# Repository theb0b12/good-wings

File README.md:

# Good Wings

- A unibody keyboard
1. basically a corne unibody with stagger

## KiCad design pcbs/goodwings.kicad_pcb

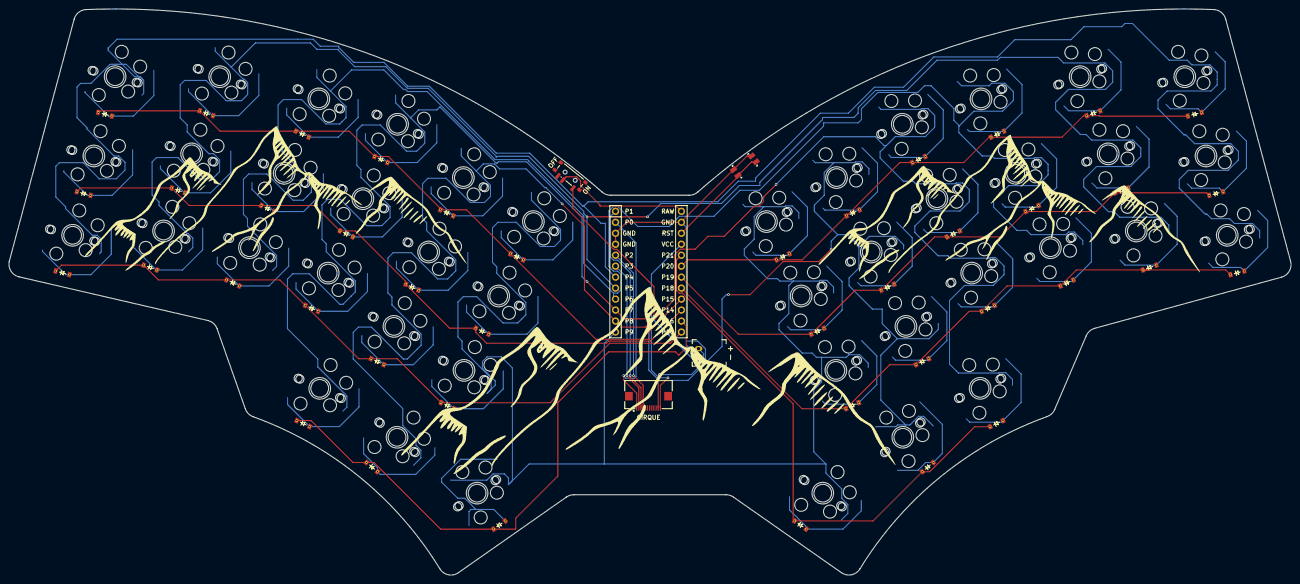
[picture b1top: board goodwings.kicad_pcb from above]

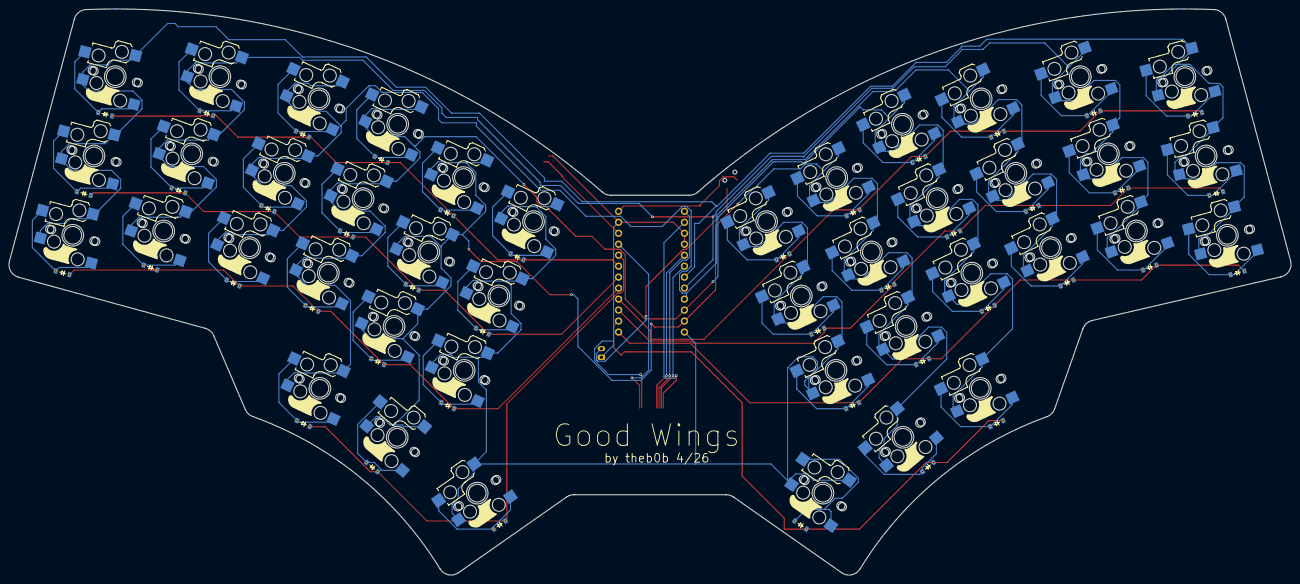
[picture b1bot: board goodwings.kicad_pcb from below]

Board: 2 copper layers, 296.7 x 131.0 mm, 131 parts (84 on the bottom side), 65 nets.

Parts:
D1, D2, D3, D4, D5, D6, D7, D8, D9, D10, D11, D12, D13, D14, D15, D16, D17, D18, D19, D20, D21, D22, D23, D24, D25, D26, D27, D28, D29, D30, D31, D32, D33, D34, D35, D36, D37, D38, D39, D40, D41, D42: ComboDiode
J2: CIRQUE; FPC-SMD_FPC05012-09200-.5mm-rev
JST1: battery_connector_jst_ph_2
MCU1: mcu_nice_nano
PWR1: power_switch_smd_side
RST1: reset_switch_smd_side
S1, S2, S3, S4, S5, S6, S7, S8, S9, S10, S11, S12, S13, S14, S15, S16, S17, S18, S19, S20, S21, S22, S23, S24, S25, S26, S27, S28, S29, S30, S31, S32, S33, S34, S35, S36, S37, S38, S39, S40, S41, S42: switch_choc_v1_v2
S43, S44, S45, S46, S47, S48, S49, S50, S51, S52, S53, S54, S55, S56, S57, S58, S59, S60, S61, S62, S63, S64, S65, S66, S67, S68, S69, S70, S71, S72, S73, S74, S75, S76, S77, S78, S79, S80, S81, S82, S83, S84: switch_mx

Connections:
BAT_P: JST1.2, PWR1.1
GND: J2.2, JST1.1, MCU1.2, MCU1.21, MCU1.22, RST1.1, RST1.3
P0: J2.12, MCU1.23
P1: J2.10, MCU1.24
P2: J2.9, MCU1.20
P3: J2.11, MCU1.19
P4: MCU1.18, S1.1, S2.1, S3.1, S22.1, S23.1, S24.1, S43.1, S44.1, S45.1, S64.1, S65.1, S66.1
P5: MCU1.17, S4.1, S5.1, S6.1, S25.1, S26.1, S27.1, S46.1, S47.1, S48.1, S67.1, S68.1, S69.1
P6: MCU1.16, S7.1, S8.1, S9.1, S28.1, S29.1, S30.1, S49.1, S50.1, S51.1, S70.1, S71.1, S72.1
P7: MCU1.15, S10.1, S11.1, S12.1, S19.1, S31.1, S32.1, S33.1, S40.1, S52.1, S53.1, S54.1, S61.1, S73.1, S74.1, S75.1, S82.1
P8: MCU1.14, S13.1, S14.1, S15.1, S20.1, S34.1, S35.1, S36.1, S41.1, S55.1, S56.1, S57.1, S62.1, S76.1, S77.1, S78.1, S83.1
P9: MCU1.13, S16.1, S17.1, S18.1, S21.1, S37.1, S38.1, S39.1, S42.1, S58.1, S59.1, S60.1, S63.1, S79.1, S80.1, S81.1, S84.1
P10: D1.1, D4.1, D7.1, D10.1, D13.1, D16.1, MCU1.12
P14: D2.1, D5.1, D8.1, D11.1, D14.1, D17.1, MCU1.10
P15: D3.1, D6.1, D9.1, D12.1, D15.1, D18.1, MCU1.9
P16: D19.1, D20.1, D21.1, MCU1.11
P18: D22.1, D25.1, D28.1, D31.1, D34.1, D37.1, MCU1.8
P19: D23.1, D26.1, D29.1, D32.1, D35.1, D38.1, MCU1.7
P20: D24.1, D27.1, D30.1, D33.1, D36.1, D39.1, MCU1.6
P21: D40.1, D41.1, D42.1, MCU1.5
RAW: MCU1.1, PWR1.2
RST: MCU1.3, RST1.2, RST1.4
VCC: J2.1, MCU1.4
c1_r1: D3.1, D3.2, S3.2, S45.2
c1_r2: D2.1, D2.2, S2.2, S44.2
c1_r3: D1.1, D1.2, S1.2, S43.2
c2_r1: D6.1, D6.2, S6.2, S48.2
c2_r2: D5.1, D5.2, S5.2, S47.2
c2_r3: D4.1, D4.2, S4.2, S46.2
c3_r1: D9.1, D9.2, S9.2, S51.2
c3_r2: D8.1, D8.2, S8.2, S50.2
c3_r3: D7.1, D7.2, S7.2, S49.2
c4_r0: D19.1, D19.2, S19.2, S61.2
c4_r1: D12.1, D12.2, S12.2, S54.2
c4_r2: D11.1, D11.2, S11.2, S53.2
c4_r3: D10.1, D10.2, S10.2, S52.2
c5_r0: D20.1, D20.2, S20.2, S62.2
c5_r1: D15.1, D15.2, S15.2, S57.2
c5_r2: D14.1, D14.2, S14.2, S56.2
c5_r3: D13.1, D13.2, S13.2, S55.2
c6_r0: D21.1, D21.2, S21.2, S63.2
c6_r1: D18.1, D18.2, S18.2, S60.2
c6_r2: D17.1, D17.2, S17.2, S59.2
c6_r3: D16.1, D16.2, S16.2, S58.2
mirror_c1_r1: D24.1, D24.2, S24.2, S66.2
mirror_c1_r2: D23.1, D23.2, S23.2, S65.2
mirror_c1_r3: D22.1, D22.2, S22.2, S64.2
mirror_c2_r1: D27.1, D27.2, S27.2, S69.2
mirror_c2_r2: D26.1, D26.2, S26.2, S68.2
mirror_c2_r3: D25.1, D25.2, S25.2, S67.2
mirror_c3_r1: D30.1, D30.2, S30.2, S72.2
mirror_c3_r2: D29.1, D29.2, S29.2, S71.2
mirror_c3_r3: D28.1, D28.2, S28.2, S70.2
mirror_c4_r0: D40.1, D40.2, S40.2, S82.2
mirror_c4_r1: D33.1, D33.2, S33.2, S75.2
mirror_c4_r2: D32.1, D32.2, S32.2, S74.2
mirror_c4_r3: D31.1, D31.2, S31.2, S73.2
mirror_c5_r0: D41.1, D41.2, S41.2, S83.2
mirror_c5_r1: D36.1, D36.2, S36.2, S78.2
mirror_c5_r2: D35.1, D35.2, S35.2, S77.2
mirror_c5_r3: D34.1, D34.2, S34.2, S76.2
mirror_c6_r0: D42.1, D42.2, S42.2, S84.2
mirror_c6_r1: D39.1, D39.2, S39.2, S81.2
mirror_c6_r2: D38.1, D38.2, S38.2, S80.2
mirror_c6_r3: D37.1, D37.2, S37.2, S79.2

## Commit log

2026-06-22 deleted bash script
